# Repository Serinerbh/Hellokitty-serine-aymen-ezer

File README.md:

# 🐱 HelloKitty – Projet Robot Chat

### **Les contributeurs :**
-BENJEMAA Aymen
-SOLTANI Ezer
-ROUABAH Serine

## 📚 Table des matières

1. [📜 Présentation générale](#-présentation-générale)
2. [📐 Architecture matérielle](#-architecture-matérielle)
   - [🔌 Schéma système](#-schéma-système)
   - [📌 Pinout STM32](#-pinout-stm32)
   - [🛠️ PCB et design électronique](#-pcb-et-design-électronique)
3. [🧩 Architecture logicielle](#-architecture-logicielle)
   - [🧱 Couches logicielles](#-couches-logicielles)
   - [🕒 Fonctionnement des tâches FreeRTOS](#-fonctionnement-des-tâches-freertos)
   - [🔄 Synchronisation et priorités](#-synchronisation-et-priorités)
4. [⚙️ Drivers et HAL](#-drivers-et-hal)
5. [🎯 Stratégie comportementale](#-stratégie-comportementale)
6. [📊 Tests et validation](#-tests-et-validation)
7. [🔧 Résultats et perspectives](#-résultats-et-perspectives)

## Présentation générale

HelloKitty est un robot mobile autonome conçu pour évoluer sur une surface plane sans bordure, dans un jeu de poursuite entre plusieurs robots. Le projet s’inscrit dans le cadre du module Systèmes Électroniques Avancés de l’ENSEA, et vise à couvrir l’ensemble du cycle de développement embarqué : de la conception du PCB à l’implémentation logicielle temps réel, en passant par la stratégie comportementale.

Le robot est capable de détecter les bords, d’éviter les chutes, de repérer d’autres robots, et de changer de rôle (chat ↔ souris) en fonction des interactions physiques ou visuelles. Le projet met en œuvre des capteurs variés, une architecture logicielle modulaire, et une gestion fine des tâches concurrentes via FreeRTOS.

## **Architecture**  
### **Schéma architectural**  

#  Architecture du système embarqué STM32G431CBU6

Ce projet repose sur un microcontrôleur **STM32G431CBU6**, intégrant divers capteurs, modules de communication, moteurs et interfaces utilisateur pour créer un système autonome capable de capter, traiter et agir dans un environnement physique.

##  Microcontrôleur central
- **STM32G431CBU6** : cœur du système, gère les communications, le traitement des données et le contrôle des périphériques.

## Alimentation
- **Batterie NiMH 7.2V 1.3Ah** : source principale d’énergie.
- **Régulateurs de tension** :
  - **MP1475DJ-LF-P** : convertit la tension en **5V**.
  - **BU33SD5WG-TR** : convertit en **3.3V** pour les composants sensibles.

## Capteurs et modules
- **4 capteurs TOF (Time-of-Flight)** : connectés via **I2C**, pour mesurer les distances.
- **Accéléromètre ADXL343** : connecté en **I2C**, pour détecter les mouvements.
- **Module Bluetooth** : communication sans fil via **UART**.
- **Lidar YDLIDAR X2** : capteur de télémétrie, connecté en **UART**.

## Horloge et programmation
- **Quartz 16MHz** : fournit une horloge stable au microcontrôleur.
- **STLink SWD** : interface de programmation et débogage.
- **Hclk** : 170Mhz.

## Moteurs et contrôle
- **2 pilotes de moteur ZXBM5210** : reçoivent des signaux **PWM** pour contrôler les moteurs gauche et droit.
- **Moteurs avec encodeurs** : permettent un retour de position et de vitesse.

## 🖱️ Interface utilisateur
- **LED** : sortie **GPIO**, pour signalisation.
- **Bouton utilisateur** : entrée **GPIO**, pour interaction manuelle.
- **Bouton reset** : pour redémarrer le système.

## 🔌 Connexions colorées
- **Rouge** : lignes d’alimentation **5V**
- **Orange** : lignes **3.3V**
- **Violet** : **I2C**
- **Bleu** : **UART**
- **Vert** : **GPIO**
- **Noir** : **PWM**

---

Ce schéma illustre l’interconnexion des modules pour un système embarqué intelligent et réactif.

## Fonctionnement interne du robot

Le robot ne se contente pas d’exécuter des actions simples : son microcontrôleur coordonne en continu l’ensemble des capteurs, moteurs et modules pour produire un comportement cohérent et réactif. Cette section décrit la logique interne qui permet au système de fonctionner de manière autonome.

### Organisation logicielle
Le logiciel embarqué est structuré en plusieurs tâches indépendantes.  
Chaque tâche s’occupe d’un domaine précis : analyse des distances, lecture des chocs, gestion des moteurs ou encore surveillance de l’environnement.  
Cette organisation évite qu’une opération bloque les autres et garantit une réactivité constante.

### Système de décision
Le robot suit une hiérarchie de priorités pour réagir correctement aux événements :
- **Sécurité immédiate** : arrêt ou retrait en cas de danger (vide, obstacle trop proche, choc).
- **Évitement** : choix de la direction la plus dégagée grâce aux données du LiDAR.
- **Déplacement normal** : progression ou patrouille lorsque l’environnement est stable.

Cette logique empêche les comportements incohérents et permet des réactions rapides.

### Gestion dynamique des moteurs
Les moteurs sont ajustés en permanence selon la situation :
- correction de trajectoire,
- adaptation de la vitesse,
- compensation en cas de résistance ou de choc.

Le microcontrôleur calcule ces ajustements en temps réel, tandis que les drivers appliquent les consignes via PWM.

### Fusion des capteurs
Les informations issues des différents capteurs sont combinées pour obtenir une vision plus fiable de l’environnement :
- les ToF surveillent les bords,
- le LiDAR analyse l’espace autour du robot,
- l’accéléromètre détecte les impacts ou blocages.

Cette fusion permet d’anticiper les risques et d’adapter le comportement du robot de manière fluide.

### États internes
Le robot fonctionne comme une machine à états, chacun correspondant à un comportement précis :
- exploration,
- évitement,
- collision détectée,
- danger de chute,
- blocage,
- repos.

Chaque état définit les actions à effectuer et les conditions pour passer à un autre état.

### Indicateurs lumineux
Les LEDs servent de retour visuel pour comprendre l’état du robot :
- clignotement rapide : alerte,
- clignotement lent : attente,
- lumière fixe : fonctionnement normal.

Elles permettent de diagnostiquer rapidement le comportement du robot sans accéder au code.

### Synchronisation des communications
Les différents protocoles (UART, SPI, I2C) fonctionnent en parallèle.  
Pour éviter les conflits, les échanges sont cadencés et certaines lectures sont prioritaires.  
Les interruptions matérielles assurent la prise en charge immédiate des événements critiques.

---

Cette architecture logicielle permet au robot d’être autonome, réactif et capable de s’adapter en temps réel à son environnement.

##  Partie Hardware

Cette section décrit l’architecture matérielle du robot, ses composants électroniques, et les schémas associés.

### 🔌 Schéma global du système
Le système repose sur un microcontrôleur **STM32G431CBU6** qui coordonne les capteurs, les moteurs, les régulateurs et les interfaces utilisateur.

---

### ⚙️ Microcontrôleur et interfaces
Le microcontrôleur est au cœur du système. Il est connecté :
- aux moteurs via des signaux **PWM** et des entrées d’encodeurs,
- aux capteurs via **UART**, **I2C**, et **GPIO**,
- à un **STLink/SWD** pour la programmation et le débogage.

---

### 🔋 Alimentation et régulation
Le robot est alimenté par une batterie **NiMH 7.2V**, régulée en deux tensions :
- **5V** via le régulateur **MP1475DJ-LF-P**,
- **3.3V** via le régulateur **BU33SD5WG-TR**.

Ces tensions alimentent les moteurs, le microcontrôleur et les capteurs sensibles.

---

### 🦾 Pilotes de moteurs
Chaque moteur est contrôlé par un circuit **ZXBM5210-SP**, avec :
- deux entrées **PWM** pour la vitesse et la direction,
- deux sorties vers le moteur (Motor+ / Motor−),
- des entrées d’encodeurs pour le retour de position.

Chaque moteur dispose de son propre driver et de ses propres signaux.

---

### 📡 Capteurs
Le système intègre :
- **4 capteurs TOF** pour la détection de bordure,
- **1 accéléromètre ADXL343** pour les chocs et mouvements,
- **1 LiDAR YDLIDAR X2** pour la cartographie et l’évitement,
- **1 module Bluetooth** pour la communication sans fil.

Tous ces capteurs sont connectés au microcontrôleur via **I2C**, **SPI**, **UART** ou **GPIO**.

---

### 🖱️ Interface utilisateur
Le robot dispose :
- de **LEDs** pour indiquer son état (obstacle, marche, pause…),
- d’un **bouton utilisateur** pour les interactions manuelles,
- d’un **bouton reset** pour redémarrer le système.
##im

---

### 🧩 Organisation des fichiers KiCad
Les schémas sont répartis en plusieurs fichiers :
- `pucontrolleur.kicad.sch` : microcontrôleur et interfaces
- `moteur1.kicad.sch` / `moteur2.kicad.sch` : circuits moteurs
- `regulateurs.kicad.sch` : alimentation
- `capteurs.kicad.sch` : capteurs et communication

---

Cette architecture matérielle permet au robot d’être autonome, réactif et modulaire. Chaque composant est interconnecté pour assurer un fonctionnement fluide et sécurisé.

https://github.com/user-attachments/assets/3a07851f-27b0-4f3c-a773-fe1d66b704f5

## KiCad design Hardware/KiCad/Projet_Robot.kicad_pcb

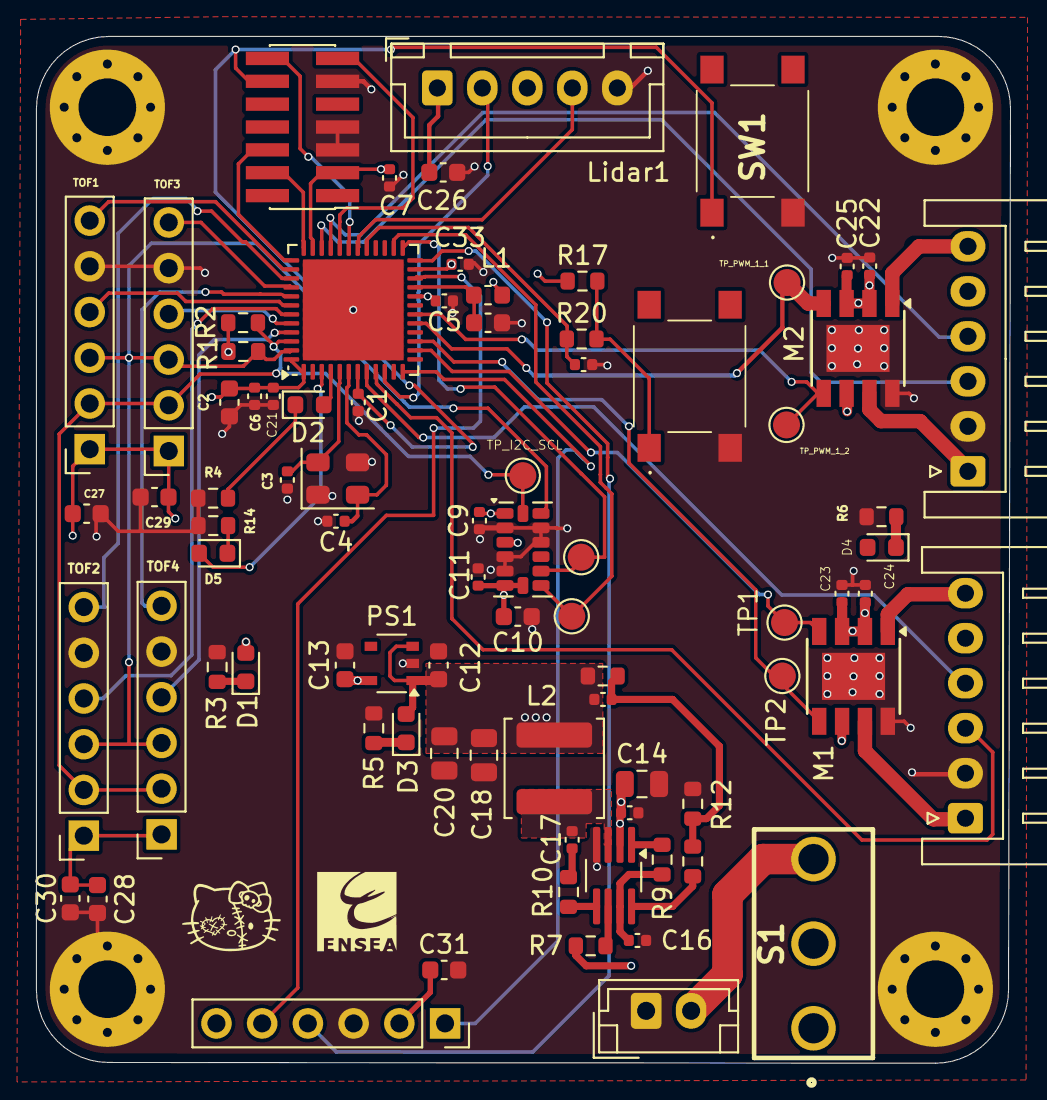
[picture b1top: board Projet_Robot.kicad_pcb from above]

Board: 4 copper layers, 54.1 x 57.0 mm, 87 parts (0 on the bottom side), 59 nets.

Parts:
Bluetooth1: Conn_01x06; PinSocket_1x06_P2.54mm_Vertical
C1, C5, C6, C7, C9, C11, C15, C16, C17, C21, C22, C23, C24, C25, C32, C33: 100n; C_0402_1005Metric
C2: 4u7; C_0603_1608Metric
C3, C4: 10p; C_0402_1005Metric
C8: 10n; C_0603_1608Metric
C10: 10u; C_0603_1608Metric
C12, C13, C26, C27, C28, C29, C30, C31: 1u; C_0603_1608Metric
C14, C18, C20: 22u; C_0805_2012Metric
C19: 15p; C_0402_1005Metric
D1, D2, D3, D4, D5: LED_Small; LED_0603_1608Metric
H1, H2, H3, H4: MountingHole_Pad; MountingHole_3.2mm_M3_Pad_Via
HelloKitty: L; logo hello
IC1: ADXL343BCCZ-RL; LGA-14_3x5mm_P0.8mm_LayoutBorder1x6y
IC2: MP1475DJ-LF-P; TSOT-23-8_HandSoldering
J1: Conn_Battery_Cell; JST_EH_B2B-EH-A_1x02_P2.50mm_Vertical
J11: Conn_ST_STDC14; PinHeader_2x07_P1.27mm_Vertical_SMD
L1: 39n; L_0603_1608Metric
L2: 4u7; L_APV_ANR5040
Lidar1: Conn_01x05; JST_XH_B5B-XH-A_1x05_P2.50mm_Vertical
M1, M2: ZXBM5210-SP; Diodes_SO-8EP
Motor1, Motor2: Conn_01x06; JST_XH_S6B-XH-A_1x06_P2.50mm_Horizontal
PS1: BU33SD5WG-TR; TSOP-5_1.65x3.05mm_P0.95mm
R1, R2: 2k2; R_0603_1608Metric
R3, R4: 600; R_0603_1608Metric
R5: 2k3; R_0603_1608Metric
R6: 4k5; R_0603_1608Metric
R7, R9: 100K; R_0603_1608Metric
R10: 20k; R_0603_1608Metric
R11: 16k; R_0603_1608Metric
R12: 7K68; R_0603_1608Metric
R13: 40k2; R_0603_1608Metric
R14: 1k6; R_0603_1608Metric
R17: 10k; R_0603_1608Metric
R20: 10K; R_0603_1608Metric
S1: 1101M2S3CQE2; 1101M2S3QE2
SW1: SW_Push; SW Push 1P1T NO 6x6mm H9.5mm
TOF1, TOF2, TOF3, TOF4: Conn_01x06; PinSocket_1x06_P2.54mm_Vertical
TP1, TP2, TP3, TP6, TP7, TP8: TestPoint; TestPoint_Pad_D1.5mm
TP_PWM_1_2: TestPoint; TestPoint_Pad_D1.5mm
U1: STM32G431CBUx; QFN-48-1EP_7x7mm_P0.5mm_EP5.6x5.6mm
Y1: 16MHz; Crystal_SMD_EuroQuartz_MT-4Pin_3.2x2.5mm
ch/sou1: SW_Push; SW Push 1P1T NO 6x6mm H9.5mm

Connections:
+3.3V: C2.2, C5.2, C6.2, C7.2, C9.2, C10.2, C11.2, C13.2, C21.2, C27.1, C28.1, C29.1, C30.1, C33.2, D1.2 (A), IC1.1 (VDD_I/O), IC1.3 (RESERVED_1), IC1.6 (VS), IC1.7 (~CS), J11.3 (VCC), L1.1, Motor1.5, Motor2.5, PS1.5 (VOUT), R1.1, R2.1, R17.1, TOF1.1, TOF2.1, TOF3.1, TOF4.1, U1.1 (VBAT), U1.20 (VREF+), U1.23 (VDD), U1.35 (VDD), U1.48 (VDD)
+5V: Bluetooth1.2, C12.1, C18.1, C19.2, C20.1, C26.1, C31.1, D3.2 (A), L2.2, Lidar1.1, PS1.1 (VIN), PS1.3 (STBY), R13.2
+VBAT: C14.1, C15.1, C22.1, C23.1, C24.2, C25.2, IC2.2 (IN), M1.2 (VM), M1.3 (VDD), M1.6 (VREF), M2.2 (VM), M2.3 (VDD), M2.6 (VREF), R7.1, S1.2
/Capteurs/ACC_INT1: IC1.8 (INT1), TP8.1, U1.26 (PB13)
/Capteurs/ACC_INT2: IC1.9 (INT2), TP7.1, U1.25 (PB12)
/Capteurs/Bluetooth_En: Bluetooth1.1, U1.12 (PA4)
/Capteurs/Bluetooth_USART3_RX: Bluetooth1.4, U1.24 (PB11)
/Capteurs/Bluetooth_USART3_TX: Bluetooth1.5, U1.22 (PB10)
/Capteurs/I2C1_SCL: IC1.14 (SCL/SCLK), R2.2, TOF1.2, TOF2.2, TOF3.2, TOF4.2, TP6.1, U1.46 (PB8)
/Capteurs/I2C1_SDA: IC1.13 (SDA/SDI/SDIO), R1.2, TOF1.3, TOF2.3, TOF3.3, TOF4.3, U1.47 (PB9)
/Capteurs/LIDAR_USART2_RX: Lidar1.2, U1.10 (PA2)
/Capteurs/M_CTR: Lidar1.4, U1.30 (PA8)
/Capteurs/TOF1_XSHUT: TOF1.6, U1.38 (PA15)
/Capteurs/TOF2_XSHUT: TOF2.6, U1.39 (PC10)
/Capteurs/TOF3_XSHUT: TOF3.6, U1.40 (PC11)
/Capteurs/TOF4_XSHUT: TOF4.6, U1.41 (PB3)
/Capteurs/tof1_GPIO: TOF1.4, U1.42 (PB4)
/Capteurs/tof2_GPIO: TOF2.4, U1.43 (PB5)
/Capteurs/tof3_GPIO: TOF3.4, U1.44 (PB6)
/Capteurs/tof4_GPIO: TOF4.4, U1.45 (PB7)
/Moteur1/ENC1_PH1: Motor1.4, U1.8 (PA0)
/Moteur1/ENC1_PH2: Motor1.3, U1.9 (PA1)
/Moteur1/Motor1+: M1.1 (OUT1), Motor1.6
/Moteur1/Motor1-: M1.7 (OUT2), Motor1.1
/Moteur1/PWM_Mot1_CH1: M1.4 (FWD), TP1.1, U1.14 (PA6)
/Moteur1/PWM_Mot1_CH2: M1.5 (REV), TP2.1, U1.15 (PA7)
/Moteur2/ENC1_PH1: Motor2.4, U1.33 (PA11)
/Moteur2/ENC1_PH2: Motor2.3, U1.34 (PA12)
/Moteur2/Motor1+: M2.1 (OUT1), Motor2.6
/Moteur2/Motor1-: M2.7 (OUT2), Motor2.1
/Moteur2/PWM_Mot1_CH1: M2.4 (FWD), TP3.1, U1.17 (PB0)
/Moteur2/PWM_Mot1_CH2: M2.5 (REV), TP_PWM_1_2.1, U1.18 (PB1)
/Régulateurs/SW: C17.2, IC2.3 (SW), L2.1
/µcontrolleur/BOUTON_Chat/Souris: C32.1, R20.1, U1.29 (PC6)
/µcontrolleur/NRST: C1.1, J11.12 (~RST), SW1.1, U1.7 (PG10)
/µcontrolleur/STATUS_CHAT_LED: D2.2 (A), U1.4 (PC15)
/µcontrolleur/STATUS_SOURIS_LED: D5.2 (A), U1.3 (PC14)
/µcontrolleur/SWCLK: J11.6 (JCLK/SWCLK), U1.37 (PA14)
/µcontrolleur/SWDIO: J11.4 (JTMS/SWDIO), U1.36 (PA13)
/µcontrolleur/VCP_RX: J11.13 (VCP_RX), U1.32 (PA10)
/µcontrolleur/VCP_TX: J11.14 (VCP_TX), U1.31 (PA9)
GND: Bluetooth1.3, C1.2, C2.1, C3.2, C4.2, C5.1, C6.1, C7.1, C8.1, C9.1, C10.1, C11.1, C12.2, C13.1, C14.2, C15.2, C16.2, C18.2, C20.2, C21.1, C22.2, C23.2, C24.1, C25.1, C26.2, C27.2, C28.2, C29.2, C30.2, C31.2, C32.2, C33.1, H1.1, H2.1, H3.1, H4.1, IC1.2 (GND_1), IC1.4 (GND_2), IC1.5 (GND_3), IC1.11 (RESERVED_2), IC1.12 (SDO/ALT_ADDRESS), IC2.4 (GND), J1.1, J11.5 (GND), J11.7 (GND), J11.11 (GNDDetect), Lidar1.5, M1.8 (GND), M1.9 (GND), M2.8 (GND), M2.9 (GND), Motor1.2, Motor2.2, PS1.2 (GND), R3.1, R4.1, R5.1, R6.1, R12.2, R14.1, SW1.2, TOF1.5, TOF2.5, TOF3.5, TOF4.5, U1.49 (VSS), Y1.1, Y1.3, ch/sou1.2
unnamed: C17.1, R10.2
unnamed: C19.1, R11.2, R12.1, R13.1
unnamed: D1.1 (K), R3.2
unnamed: D2.1 (K), R4.2
unnamed: D3.1 (K), R5.2
unnamed: D4.1 (K), R6.2
unnamed: D5.1 (K), R14.2
unnamed: IC2.5 (BST), R10.1
unnamed: IC2.6 (EN/SYNC), R7.2
unnamed: IC2.8 (FB), R11.1
unnamed: IC2.1 (PG), R9.2
unnamed: C16.1, IC2.7 (VCC), R9.1
unnamed: J1.2, S1.3
unnamed: R17.2, R20.2, ch/sou1.1
unnamed: C3.1, U1.5 (PF0), Y1.4
unnamed: C4.1, U1.6 (PF1), Y1.2
unnamed: C8.2, L1.2, U1.21 (VDDA)

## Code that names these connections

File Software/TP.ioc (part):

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Mcu.Name=STM32G431C(6-8-B)Ux
Mcu.Package=UFQFPN48
Mcu.UserName=STM32G431CBUx
PA0.GPIOParameters=GPIO_Label
PA0.GPIO_Label=PWM_Mot1_CH1
PA0.Signal=S_TIM2_CH1
PA1.GPIOParameters=GPIO_Label
PA1.GPIO_Label=PWM_Mot1_CH2
PA1.Signal=S_TIM2_CH2
PA10.GPIOParameters=GPIO_Label
PA10.GPIO_Label=VCP_RX
PA10.Mode=Asynchronous
PA10.Signal=USART1_RX
PA11.GPIOParameters=GPIO_Label
PA11.GPIO_Label=PWM_Mot2_CH1
PA11.Signal=S_TIM4_CH1
PA12.GPIOParameters=GPIO_Label
PA12.GPIO_Label=PWM_Mot2_CH2
PA12.Signal=S_TIM4_CH2
PA13.Mode=Serial_Wire
PA13.Signal=SYS_JTMS-SWDIO
PA14.Mode=Serial_Wire
PA14.Signal=SYS_JTCK-SWCLK
PA15.GPIOParameters=GPIO_Label
PA15.GPIO_Label=TOF1_XSHUT
PA15.Signal=GPIO_Output
PA2.GPIOParameters=GPIO_Label
PA2.GPIO_Label=LIDAR_RX
PA2.Mode=Half_duplex(single_wire_mode)
PA2.Signal=USART2_TX
PA6.GPIOParameters=GPIO_Label
PA6.GPIO_Label=ENC1_PH1
PA6.Signal=S_TIM3_CH1
PA7.GPIOParameters=GPIO_Label
PA7.GPIO_Label=ENC1_PH2
PA7.Signal=S_TIM3_CH2
PA8.GPIOParameters=GPIO_Label
PA8.GPIO_Label=M_CTR
PA8.Signal=S_TIM1_CH1
PA9.GPIOParameters=GPIO_Label
PA9.GPIO_Label=VCP_TX
PA9.Mode=Asynchronous
PA9.Signal=USART1_TX
PB0.GPIOParameters=GPIO_Label
PB0.GPIO_Label=ENC2_PH1
PB0.Signal=S_TIM3_CH3
PB1.GPIOParameters=GPIO_Label
PB1.GPIO_Label=ENC2_PH2
PB1.Signal=S_TIM3_CH4
PB10.GPIOParameters=GPIO_Label
PB10.GPIO_Label=Bluetooth_TX
PB10.Mode=Asynchronous
PB10.Signal=USART3_TX
PB11.GPIOParameters=GPIO_Label
PB11.GPIO_Label=Bluetooth_RX
PB11.Mode=Asynchronous
PB11.Signal=USART3_RX
PB12.GPIOParameters=GPIO_Label
PB12.GPIO_Label=ACC_INT2
PB12.Signal=GPIO_Input
PB13.GPIOParameters=GPIO_Label
PB13.GPIO_Label=ACC_INT1
PB13.Signal=GPIO_Input
PB3.GPIOParameters=GPIO_Label
PB3.GPIO_Label=TOF4_XSHUT
PB3.Signal=GPIO_Output
PB4.GPIOParameters=GPIO_Label
PB4.GPIO_Label=TOF1_GPIO
PB4.Signal=GPIO_Output
PB5.GPIOParameters=GPIO_Label
PB5.GPIO_Label=TOF2_GPIO
PB5.Signal=GPIO_Output
PB6.GPIOParameters=GPIO_Label
PB6.GPIO_Label=TOF3_GPIO
PB6.Signal=GPIO_Output
PB7.GPIOParameters=GPIO_Label
PB7.GPIO_Label=TOF4_GPIO
PB7.Signal=GPIO_Output
PB8-BOOT0.Mode=I2C
PB8-BOOT0.Signal=I2C1_SCL
PB9.Mode=I2C
PB9.Signal=I2C1_SDA
PC10.GPIOParameters=GPIO_Label
PC10.GPIO_Label=TOF2_XSHUT
PC10.Signal=GPIO_Output
PC11.GPIOParameters=GPIO_Label
PC11.GPIO_Label=TOF3_XSHUT
PC11.Signal=GPIO_Output
PC14-OSC32_IN.GPIOParameters=GPIO_Label
PC14-OSC32_IN.GPIO_Label=STATUS_SOURIS_LED
PC14-OSC32_IN.Signal=GPIO_Output
PC15-OSC32_OUT.GPIOParameters=GPIO_Label
PC15-OSC32_OUT.GPIO_Label=STATUS_CHAT_LED
PC15-OSC32_OUT.Signal=GPIO_Output
PC6.GPIOParameters=GPIO_Label
PC6.GPIO_Label=BOUTON_Chat/Souris
PC6.Signal=GPIO_Input
PF0-OSC_IN.Mode=HSE-External-Oscillator
PF0-OSC_IN.Signal=RCC_OSC_IN
PF1-OSC_OUT.Mode=HSE-External-Oscillator
PF1-OSC_OUT.Signal=RCC_OSC_OUT
PG10-NRST.GPIOParameters=GPIO_Label
PG10-NRST.GPIO_Label=BOUTON_RESET
PG10-NRST.Signal=GPIO_Input
RCC.HSE_VALUE=16000000
RCC.SYSCLKFreq_VALUE=16000000
RCC.SYSCLKSource=RCC_SYSCLKSOURCE_HSE
board=custom

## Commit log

2025-09-23 change
2025-09-23 delete
2025-09-23 Robot
2025-09-24 review pcb
2025-09-24 1
    u
2025-09-29 CubeMX
2025-09-30 hhhh
2025-09-30 s
    s
2025-10-01 Ezer
2025-10-01 11111
2025-10-06 AAAAAAAAAAA
2025-10-06 AAAA
2025-10-06 4444
2025-10-07 AAAAAAA
2025-10-09 test
2025-10-13 check LF
2025-10-13 gerbers
2025-11-12 Firmware
2025-11-18 structure
2025-11-18 test motor
2025-11-27 tof test
2025-12-02 Ajout des tests unitaires : accéléromètre et LIDAR
2025-12-02 mise a jour du test moteur 1
2025-12-02 Test_encodeur _RPM_Rads
2025-12-02 Ajout du support pour 4 capteurs VL53L0X
2025-12-02 enc_mot_drv
2025-12-03 code Drivers HC_05
2025-12-09 Driver Lidar & Accelerometre
2025-12-09 Encodeur
2025-12-09 Structure Firmware
2025-12-09 Update driver Lidar & IMU
2025-12-09 Intégration FreeRTOS
2025-12-10 intégration des tâches FreeRTOS : Lidar & Accélerometre
2025-12-13 Intégration FreeRTOS avec drivers Lidar, IMU, TOF et moteurs
2026-01-01 asservissement PID, sécurité TOF par interruption et filtrage LIDAR
2026-01-09 Implémentation architecture FreeRTOS (Control, Safety, Lidar, IMU)
2026-01-09 implémentation de la stratégie, du suivi de cible et du contrôle Bluetooth
    - Ajout de la machine à états (RECHERCHE, ATTAQUE, FUITE) dans strategy.c.
    - Implémentation du changement de rôle dynamique (Chat/Souris) par détection de chocs (IMU).
    - Ajout du suivi de cible LIDAR avec lissage temporel (filtre Alpha).
    - Mise en place du contrôle Bluetooth (HC-05) : commandes START, STOP, CHAT, SOURIS.
    - Redirection des logs de debug (printf) vers l'UART Bluetooth (9600 bauds).
    - Intégration complète sous FreeRTOS avec des cycles d'exécution de 10Hz à 100Hz.
2026-01-09 implémentation complète de la stratégie de combat et finalisation du firmware
2026-01-14 Revise README for HelloKitty robot project
    Updated project title and added detailed table of contents with sections on hardware and software architecture, drivers, and testing.
2026-01-14 TOF mode Polling
2026-01-14 update TOF task
2026-01-14 passage des TOF en polling et optimisation de l'anti-chute
2026-01-15 Version Finale
2026-01-15 update robot Detecet closest object + update strategy
2026-01-15 Enhance README with architecture and component details
    Added detailed architecture and component descriptions for the HelloKitty robot project.
2026-01-16 Remove global system diagram from README
    Removed the global system diagram image from the README.
2026-01-16 UPDATE lidar + strategy
2026-01-16 Fix formatting and update section titles in README
    Correct formatting and improve section titles in README.
